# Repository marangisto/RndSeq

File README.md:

# RndSeq
Random Sequence Generator

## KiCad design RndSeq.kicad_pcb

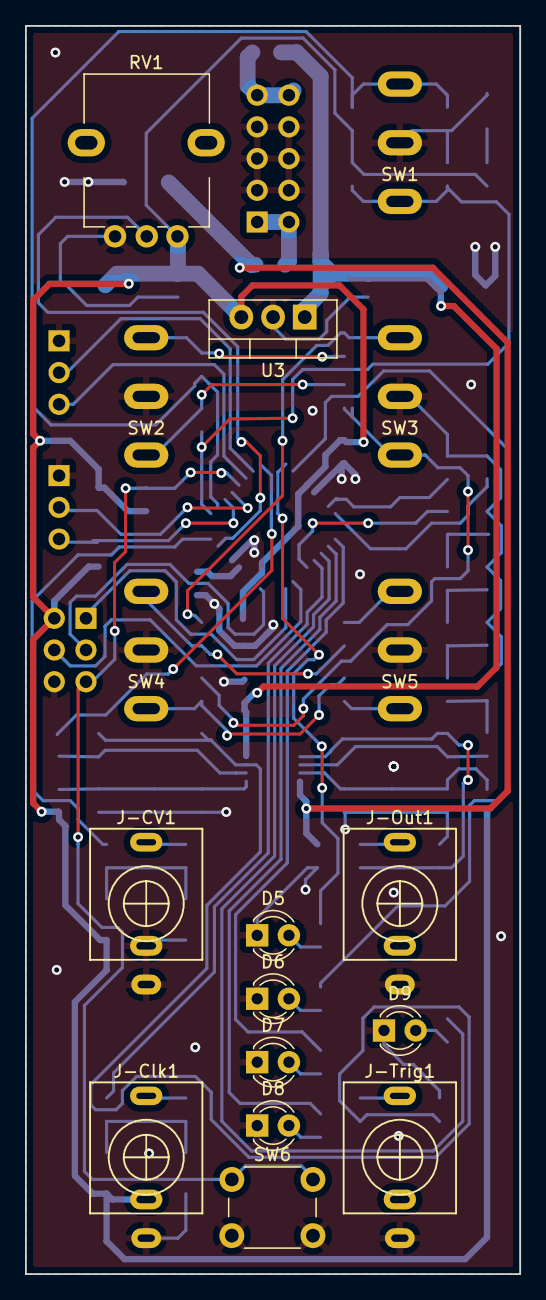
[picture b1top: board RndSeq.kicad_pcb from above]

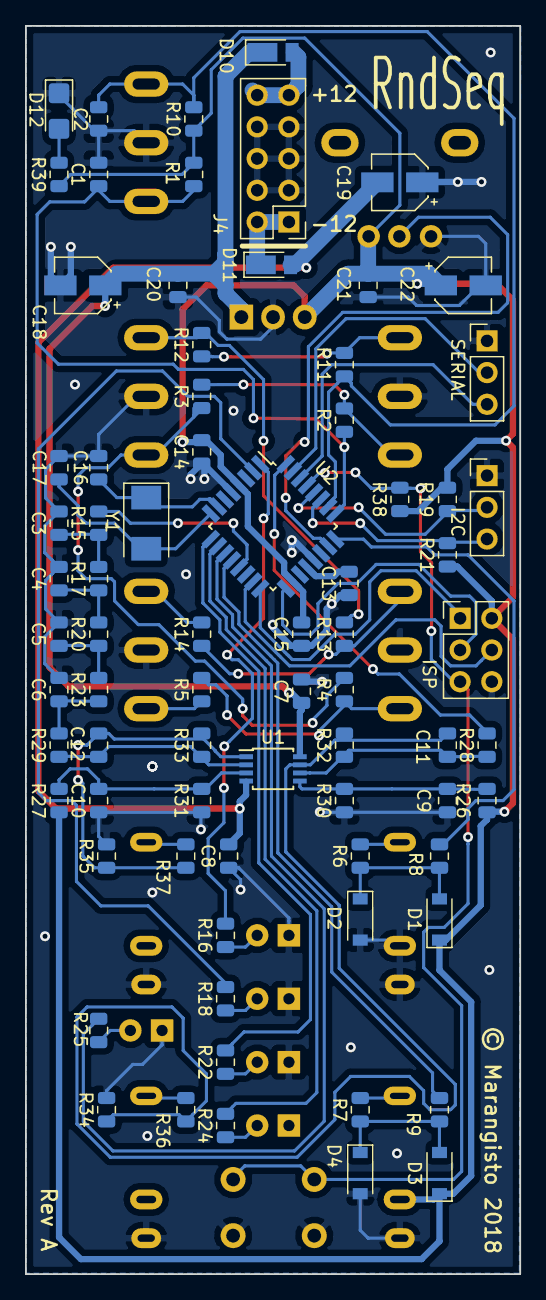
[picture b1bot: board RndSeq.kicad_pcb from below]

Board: 2 copper layers, 39.6 x 100.0 mm, 92 parts (75 on the bottom side), 59 nets.

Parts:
C1, C2, C7, C8, C9, C10, C13, C14, C15, C20, C21: 100n; C_0805_2012Metric
C3, C4, C5, C6: 47n; C_0805_2012Metric
C11, C12: 470p; C_0805_2012Metric
C16, C17: 22p; C_0805_2012Metric
C18, C19, C22: 10u; CP_Elec_4x5.8
D1, D2, D3, D4: 1N5819; D_SOD-123
D5, D6, D7, D8, D9: LED; LED_D3.0mm
D10, D11: DFLR1400-7; D_PowerDI-123
D12: LED; LED_1206_3216Metric_Castellated
I2C: Conn_01x03; PinHeader_1x03_P2.54mm_Vertical
ISP: Conn_02x03_Odd_Even; PinHeader_2x03_P2.54mm_Vertical
J4: Conn_02x05_Odd_Even; PinHeader_2x05_P2.54mm_Vertical
J-CV1: AudioJack2_Ground_Switch; PJ398SM
J-Clk1: AudioJack2_Ground_Switch; PJ398SM
J-Out1: AudioJack2_Ground_Switch; PJ398SM
J-Trig1: AudioJack2_Ground_Switch; PJ398SM
R1, R4, R10, R13, R15, R17, R20, R23, R36, R37: 1k; R_0805_2012Metric
R2, R11: 220; R_0805_2012Metric
R3, R12: 470; R_0805_2012Metric
R5, R14: 3k3; R_0805_2012Metric
R6, R7, R8, R9: 33k; R_0805_2012Metric
R16, R18, R22, R24, R25, R39: 330; R_0805_2012Metric
R19, R21: 4k7; R_0805_2012Metric
R26, R27, R28, R29, R30, R31, R32, R33: 47k; R_0805_2012Metric
R34, R35: 100k; R_0805_2012Metric
R38: 10k; R_0805_2012Metric
RV1: 100k; AlpsRK09K
SERIAL: Conn_01x03; PinHeader_1x03_P2.54mm_Vertical
SW1, SW2, SW3, SW4, SW5: SW_SPDT_MSM; SP1MS1
SW6: SW_Push; SW_PUSH_6mm_H9.5mm
U1: TL072; TSSOP-8_3x3mm_P0.65mm
U2: ATmega328PB-AU; TQFP-32_7x7mm_P0.8mm
U3: L7805; TO-220-3_Vertical
Y1: 20MHz; Crystal_SMD_Abracon_ABM3-2Pin_5.0x3.2mm

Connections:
+5V: C14.1, C15.2, C21.1, C22.1, D1.1, D3.1, ISP.2, J-Clk1.TN, R1.1, R10.1, R19.1, R21.1, R26.2, R27.2, R38.1, R39.1, RV1.1, U2.4, U2.18, U3.3
+12V: C7.1, C18.1, C20.1, D10.1, U1.8, U3.1
-12V: C8.2, C19.2, D11.2, U1.4
/MCU328/PB0: R9.1, U2.12
/MCU328/PB1: R15.2, U2.13
/MCU328/PC0: RV1.2, U2.23
/MCU328/PC1: R8.1, U2.24
/MCU328/PC2: C1.1, R1.2, R2.1, SW1.1, U2.25
/MCU328/PC3: C2.1, R10.2, R11.1, SW1.3, U2.26
/MCU328/PD2: R28.2, U2.32
/MCU328/PD3: R16.1, U2.1
/MCU328/PD4: R18.1, U2.2
/MCU328/PD5: R22.1, U2.9
/MCU328/PD6: R24.1, U2.10
/MCU328/PD7: R25.1, U2.11
/MCU328/RXD/PD0: SERIAL.3, U2.30
/MCU328/TXD/PD1: SERIAL.2, U2.31
GND: C1.2, C2.2, C3.2, C4.2, C5.2, C6.2, C7.2, C8.1, C9.2, C10.2, C13.1, C14.2, C15.1, C16.1, C17.1, C18.2, C19.1, C20.2, C21.2, C22.2, D2.2, D4.2, D5.1, D6.1, D7.1, D8.1, D9.1, D12.1, I2C.1, ISP.6, J4.3, J4.4, J4.5, J4.6, J4.7, J4.8, J-CV1.S, J-CV1.TN, J-Clk1.S, J-Out1.S, J-Trig1.S, R30.1, R31.1, R34.2, R35.2, RV1.3, SERIAL.1, SW1.2, SW2.2, SW3.2, SW4.2, SW5.2, SW6.2, U2.5, U2.21, U3.2
unnamed: C3.1, R15.1, R17.2
unnamed: C4.1, R17.1, R20.2
unnamed: C5.1, R20.1, R23.2
unnamed: C6.1, R23.1, R29.2
unnamed: C9.1, R26.1, R30.2, U1.5
unnamed: C10.1, R27.1, R31.2, U1.3
unnamed: C11.1, R32.1, R34.1, R36.2, U1.7
unnamed: C11.2, R28.1, R32.2, U1.6
unnamed: C12.1, R33.1, R35.1, R37.2, U1.1
unnamed: C12.2, R29.1, R33.2, U1.2
unnamed: C13.2, U2.20
unnamed: C16.2, U2.7, Y1.1
unnamed: C17.2, U2.8, Y1.2
unnamed: D1.2, D2.1, R6.1, R8.2
unnamed: D3.2, D4.1, R7.1, R9.2
unnamed: D5.2, R16.2
unnamed: D6.2, R18.2
unnamed: D7.2, R22.2
unnamed: D8.2, R24.2
unnamed: D9.2, R25.2
unnamed: D10.2, J4.9, J4.10
unnamed: D11.1, J4.1, J4.2
unnamed: D12.2, R39.2
unnamed: ISP.1, U2.16
unnamed: ISP.3, U2.17
unnamed: ISP.4, U2.15
unnamed: ISP.5, R38.2, SW6.1, U2.29
unnamed: J-CV1.T, R6.2
unnamed: J-Clk1.T, R7.2
unnamed: J-Out1.T, R37.1
unnamed: J-Trig1.T, R36.1
unnamed: R2.2, R3.1, SW2.1
unnamed: R3.2, R4.1, SW3.1
unnamed: R4.2, R5.1, SW4.1
unnamed: R5.2, SW5.1
unnamed: R11.2, R12.1, SW2.3
unnamed: R12.2, R13.1, SW3.3
unnamed: R13.2, R14.1, SW4.3
unnamed: R14.2, SW5.3
SCL: I2C.2, R19.2, U2.28
SDA: I2C.3, R21.2, U2.27

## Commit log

2018-08-19 Added new KiCad project.
2018-08-19 Initial schematic design.
2018-08-19 Assigned footprints.
2018-08-19 Initial board sizing and layout.
2018-08-19 Picture of initial challenge.
2018-08-19 Placement in progress...
2018-08-19 Routed all signals.
2018-08-19 Routed all power.
2018-08-19 Tidy up tracks.
2018-08-19 Finished routing.
2018-08-19 Generated Gerbers.
2018-08-19 Gerber adjustments.
2018-09-08 Added html BOM.
2018-09-08 Added CSV BOM.
2018-09-08 Use CSV BOM.

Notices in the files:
RndSeq.kicad_pcb:
© Marangisto 2018
